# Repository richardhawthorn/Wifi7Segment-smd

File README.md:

### Features

- 0.56" 7 segment display, 4 character
- ESP8266 ESP7/12/12E Processor
- Wifi connected
- HT16K33 i2c LED driver
- FTDI chip built in
- TX & RX LED indicators
- 3.3V operation
- Mini USB power connector
- FTDI programming port
- Surface mount technology

### License

This work is licensed under a Creative Commons Attribution-ShareAlike 4.0 International License.

<br />
Designed by <a xmlns:cc="http://creativecommons.org/ns#" href="http://www.richardhawthorn.com" property="cc:attributionName" rel="cc:attributionURL" target="_blank">Richard Hawthorn</a><br />
<a rel="license" href="http://creativecommons.org/licenses/by-sa/4.0/" target="_blank">View License</a>

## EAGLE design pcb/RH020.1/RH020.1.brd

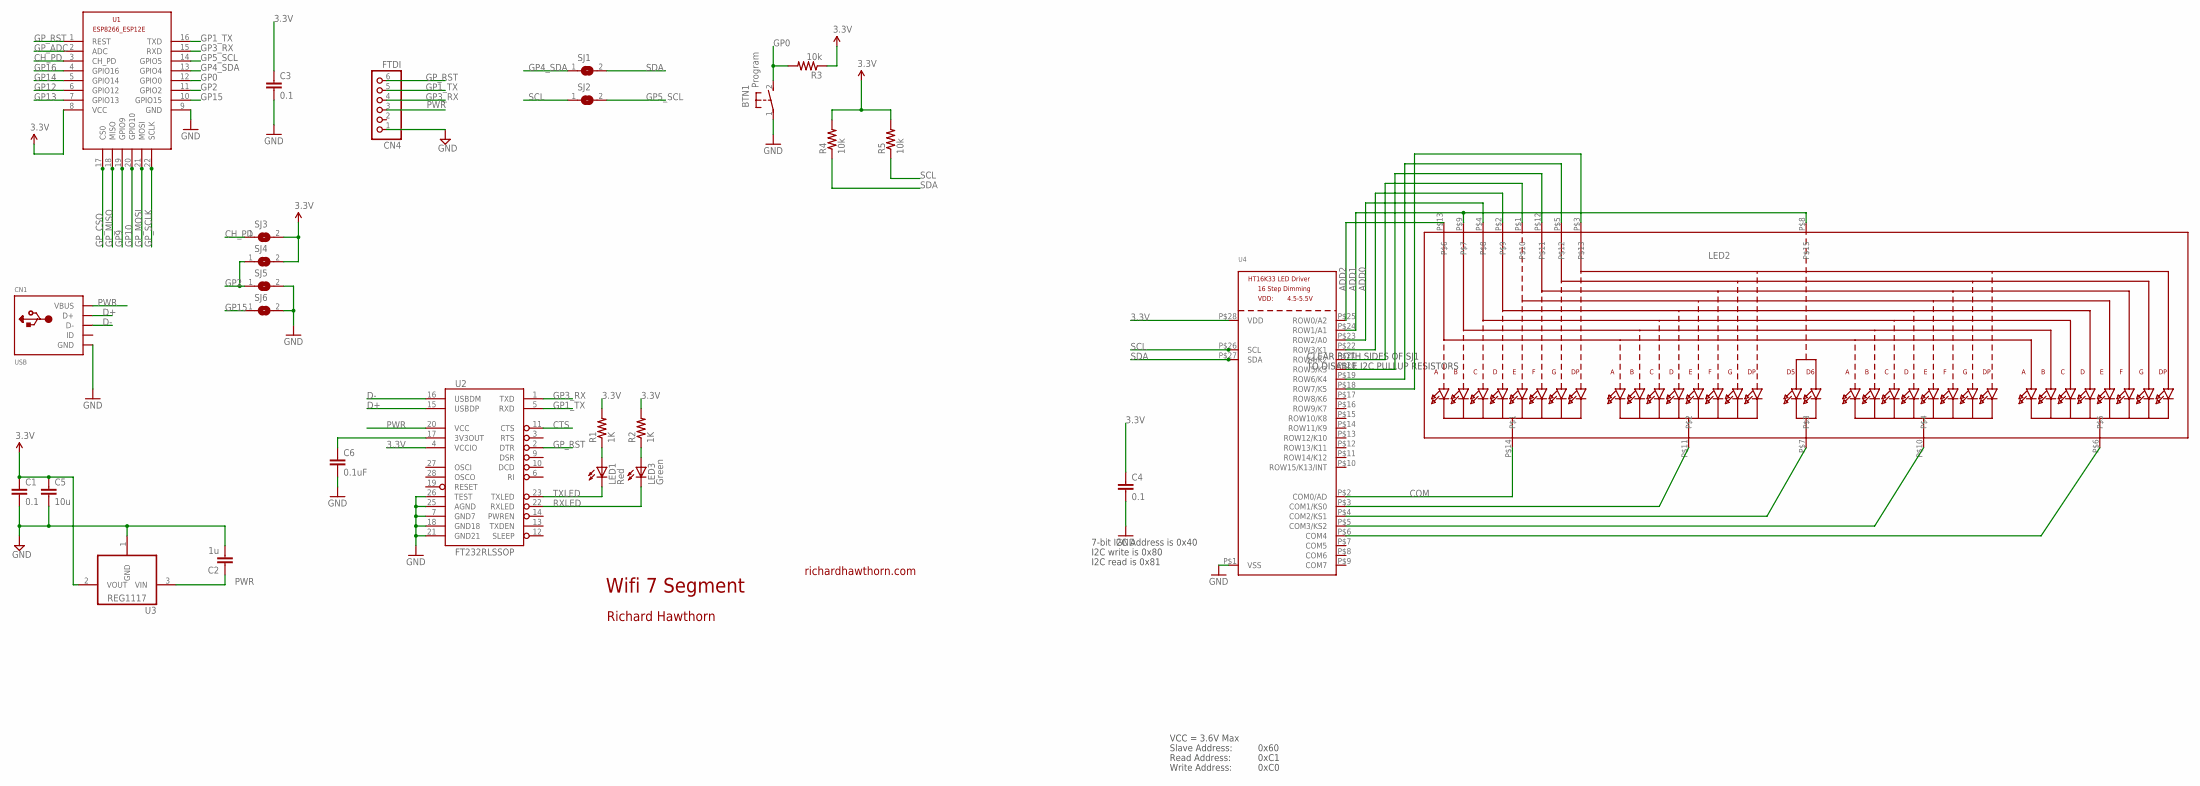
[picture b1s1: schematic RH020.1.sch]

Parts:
BTN1: Program; DTS-3
C1, C3, C4: 0.1; 0603-CAP
C2: 1u; 0603-CAP
C5: 10u; 0805-CAP
C6: 0.1uF; 0402-CAP
CN1: USB; USB-MINIB
CN4: FTDI; 1X06
LED1: Red; LED-0603
LED2: DISP_SEGMENT_4DIGIT_BL-Q56C43; SEGMENT-BL-Q56C43
LED3: Green; LED-0603
R1, R2: 1K; 0402-RES
R3, R4, R5: 10k; 0805
SJ1, SJ2, SJ3, SJ4, SJ5, SJ6: SJ
U1: ESP8266-12EESP8266-ESP12E; ESP8266-ESP12E
U2: FT232RLSSOP; SSOP28DB
U3: REG1117; SOT223
U4: HT16K33_SOP28; SOP28_300MIL

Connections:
3.3V: C1.1, C3.1, C4.1, C5.1, R1.2, R2.2, R3.1, R4.2, R5.2, SJ3.2, SJ4.2, U1.8 (VCC), U2.4 (VCCIO), U3.2 (VOUT), U4.P$28 (VDD)
3.3VOUT: C6.1, U2.17 (3V3OUT)
ADD0: LED2.P$4, U4.P$23 (ROW2/A0)
ADD1: LED2.P$8, LED2.P$9, U4.P$24 (ROW1/A1)
ADD2: LED2.P$13, U4.P$25 (ROW0/A2)
CH_PD: SJ3.1, U1.3 (CH_PD)
COM: LED2.P$14, U4.P$2 (COM0/AD)
CTS: U2.11 (CTS)
D+: CN1.D+, U2.15 (USBDP)
D-: CN1.D-, U2.16 (USBDM)
GND: BTN1.1, C1.2, C2.2, C3.2, C4.2, C5.2, C6.2, CN1.GND, CN4.1, SJ5.2, SJ6.2, U1.9 (GND), U2.7 (GND7), U2.18 (GND18), U2.21 (GND21), U2.25 (AGND), U2.26 (TEST), U3.1 (GND), U4.P$1 (VSS)
GP0: BTN1.2, R3.2, U1.12 (GPIO0)
GP1_TX: CN4.5, U1.16 (TXD), U2.5 (RXD)
GP2: SJ4.1, SJ5.1, U1.11 (GPIO2)
GP3_RX: CN4.4, U1.15 (RXD), U2.1 (TXD)
GP4_SDA: SJ1.1, U1.13 (GPIO4)
GP5_SCL: SJ2.2, U1.14 (GPIO5)
GP9: U1.19 (GPIO9)
GP10: U1.20 (GPIO10)
GP12: U1.6 (GPIO12)
GP13: U1.7 (GPIO13)
GP14: U1.5 (GPIO14)
GP15: SJ6.1, U1.10 (GPIO15)
GP16: U1.4 (GPIO16)
GP_ADC: U1.2 (ADC)
GP_CSO: U1.17 (CS0)
GP_MISO: U1.18 (MISO)
GP_MOSI: U1.21 (MOSI)
GP_RST: CN4.6, U1.1 (REST), U2.2 (DTR)
GP_SCLK: U1.22 (SCLK)
unnamed: LED1.A, R1.1
unnamed: LED3.A, R2.1
unnamed: LED2.P$11, U4.P$3 (COM1/KS0)
unnamed: LED2.P$7, U4.P$4 (COM2/KS1)
unnamed: LED2.P$10, U4.P$5 (COM3/KS2)
unnamed: LED2.P$6, U4.P$6 (COM4)
unnamed: LED2.P$2, U4.P$22 (ROW3/K1)
unnamed: LED2.P$1, U4.P$21 (ROW4/K2)
unnamed: LED2.P$12, U4.P$20 (ROW5/K3)
unnamed: LED2.P$5, U4.P$19 (ROW6/K4)
unnamed: LED2.P$3, U4.P$18 (ROW7/K5)
PWR: C2.1, CN1.VBUS, CN4.3, U2.20 (VCC), U3.3 (VIN)
RXLED: LED3.C, U2.22 (RXLED)
SCL: R5.1, SJ2.1, U4.P$26 (SCL)
SDA: R4.1, SJ1.2, U4.P$27 (SDA)
TXLED: LED1.C, U2.23 (TXLED)

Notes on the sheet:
Wifi 7 Segment
richardhawthorn.com
Richard Hawthorn
CLEAR BOTH SIDES OF SJ1
TO DISABLE I2C PULLUP RESISTORS
7-bit I2C Address is 0x40
I2C write is 0x80
I2C read is 0x81
VCC = 3.6V Max
Read Address:
Write Address:
Slave Address:
0x60
0xC1
0xC0

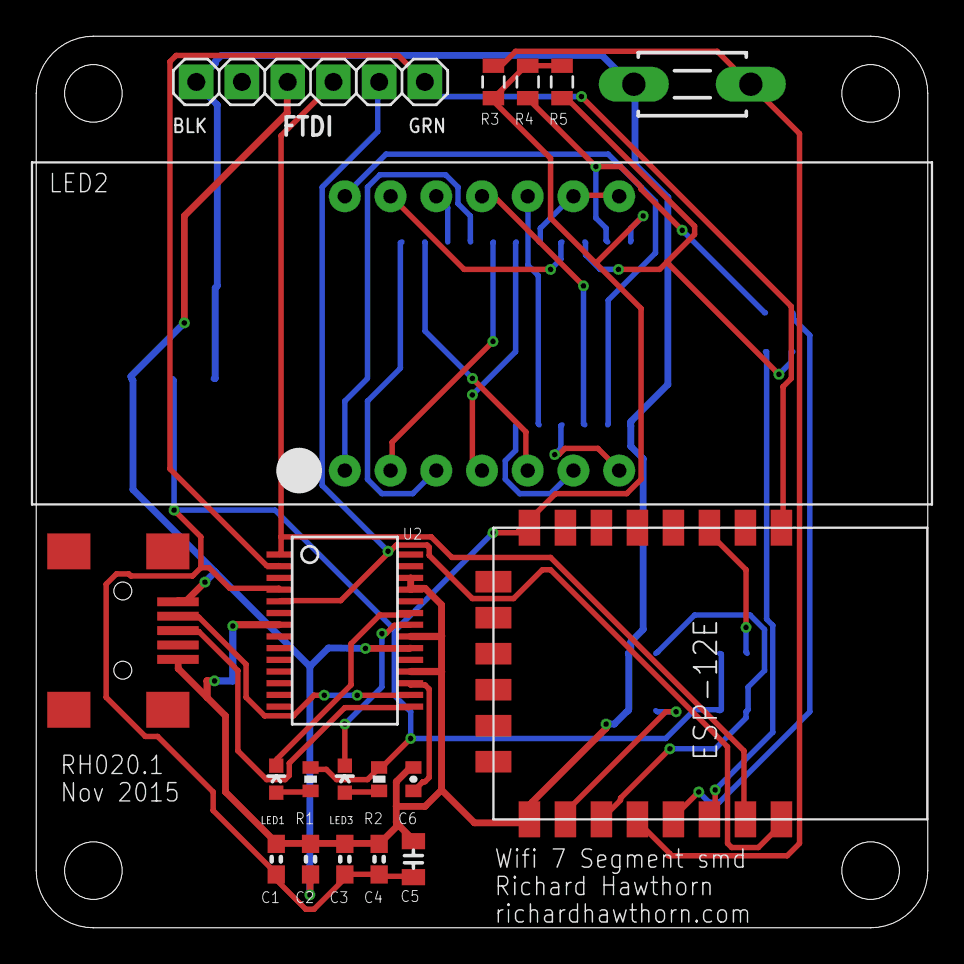
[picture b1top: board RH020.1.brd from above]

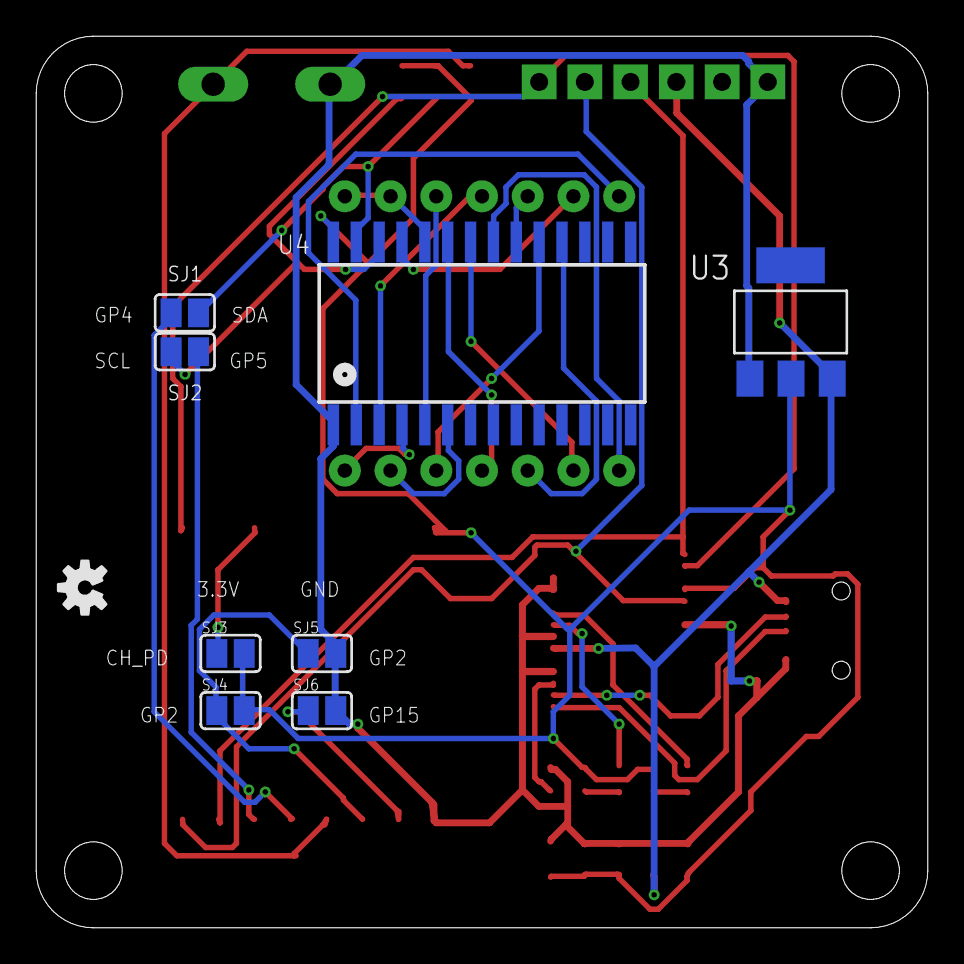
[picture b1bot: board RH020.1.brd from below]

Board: 2 copper layers, 49.5 x 49.5 mm, 28 parts (9 on the bottom side), 34 nets.

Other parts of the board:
U$3: OSHW-LOGO-S

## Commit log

2015-11-10 first version
2015-11-10 added gerbers
2015-11-10 added images
2015-12-01 updated pcb design and gerbers
2016-01-03 add images
2016-01-03 update gitignore
2016-01-03 add readme

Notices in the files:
parts and their libraries:
SparkFun-Aesthetics: Licensing: CC v3.0 Share-Alike You are welcome to use this library for commercial purposes.
